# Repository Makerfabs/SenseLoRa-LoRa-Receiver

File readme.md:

# SENSELORA LORA RECEIVER

```c++
/*
Version:		V1.0
Author:			Vincent
Create Date:	2023/9/16
Note:

*/
```
# Makerfabs

[Makerfabs home page](https://www.makerfabs.com/)

[Makerfabs Wiki](https://wiki.makerfabs.com/)

# How To Use

## Arduino Complier Option

**If you have any questions，such as how to install the development board, how to download the code, how to install the library. Please refer to :[Makerfabs_FAQ](https://github.com/Makerfabs/Makerfabs_FAQ)**

- Please disconnect from the electrical equipment before burning!
- Do not burn with alternating current!
- Open Arduino IDE
- Open boards Manager, search "RP2040"
- Install board:  Arduino Mbed OS RP2040 Boards(Version 4.0.4)

Arduino libraries:

- RP2040_SD 1.0.1  
- RadioLib 4.6.0  
- Adafruit_GFX_Library 1.11.5  
- Adafruit_BusIO 1.14.1  
- Adafruit_SSD1306 2.5.1  

## Data Analysis

Once the device is plugged in, run data_analysis.py and the serial port will be found automatically. In addition, the json data uploaded by the device is classified according to ID and stored into different CSV files.

Make sure that no other serial device is connected, or modify the Python program yourself.

Environment:

- Python      3.11.2
- pyserial    3.5

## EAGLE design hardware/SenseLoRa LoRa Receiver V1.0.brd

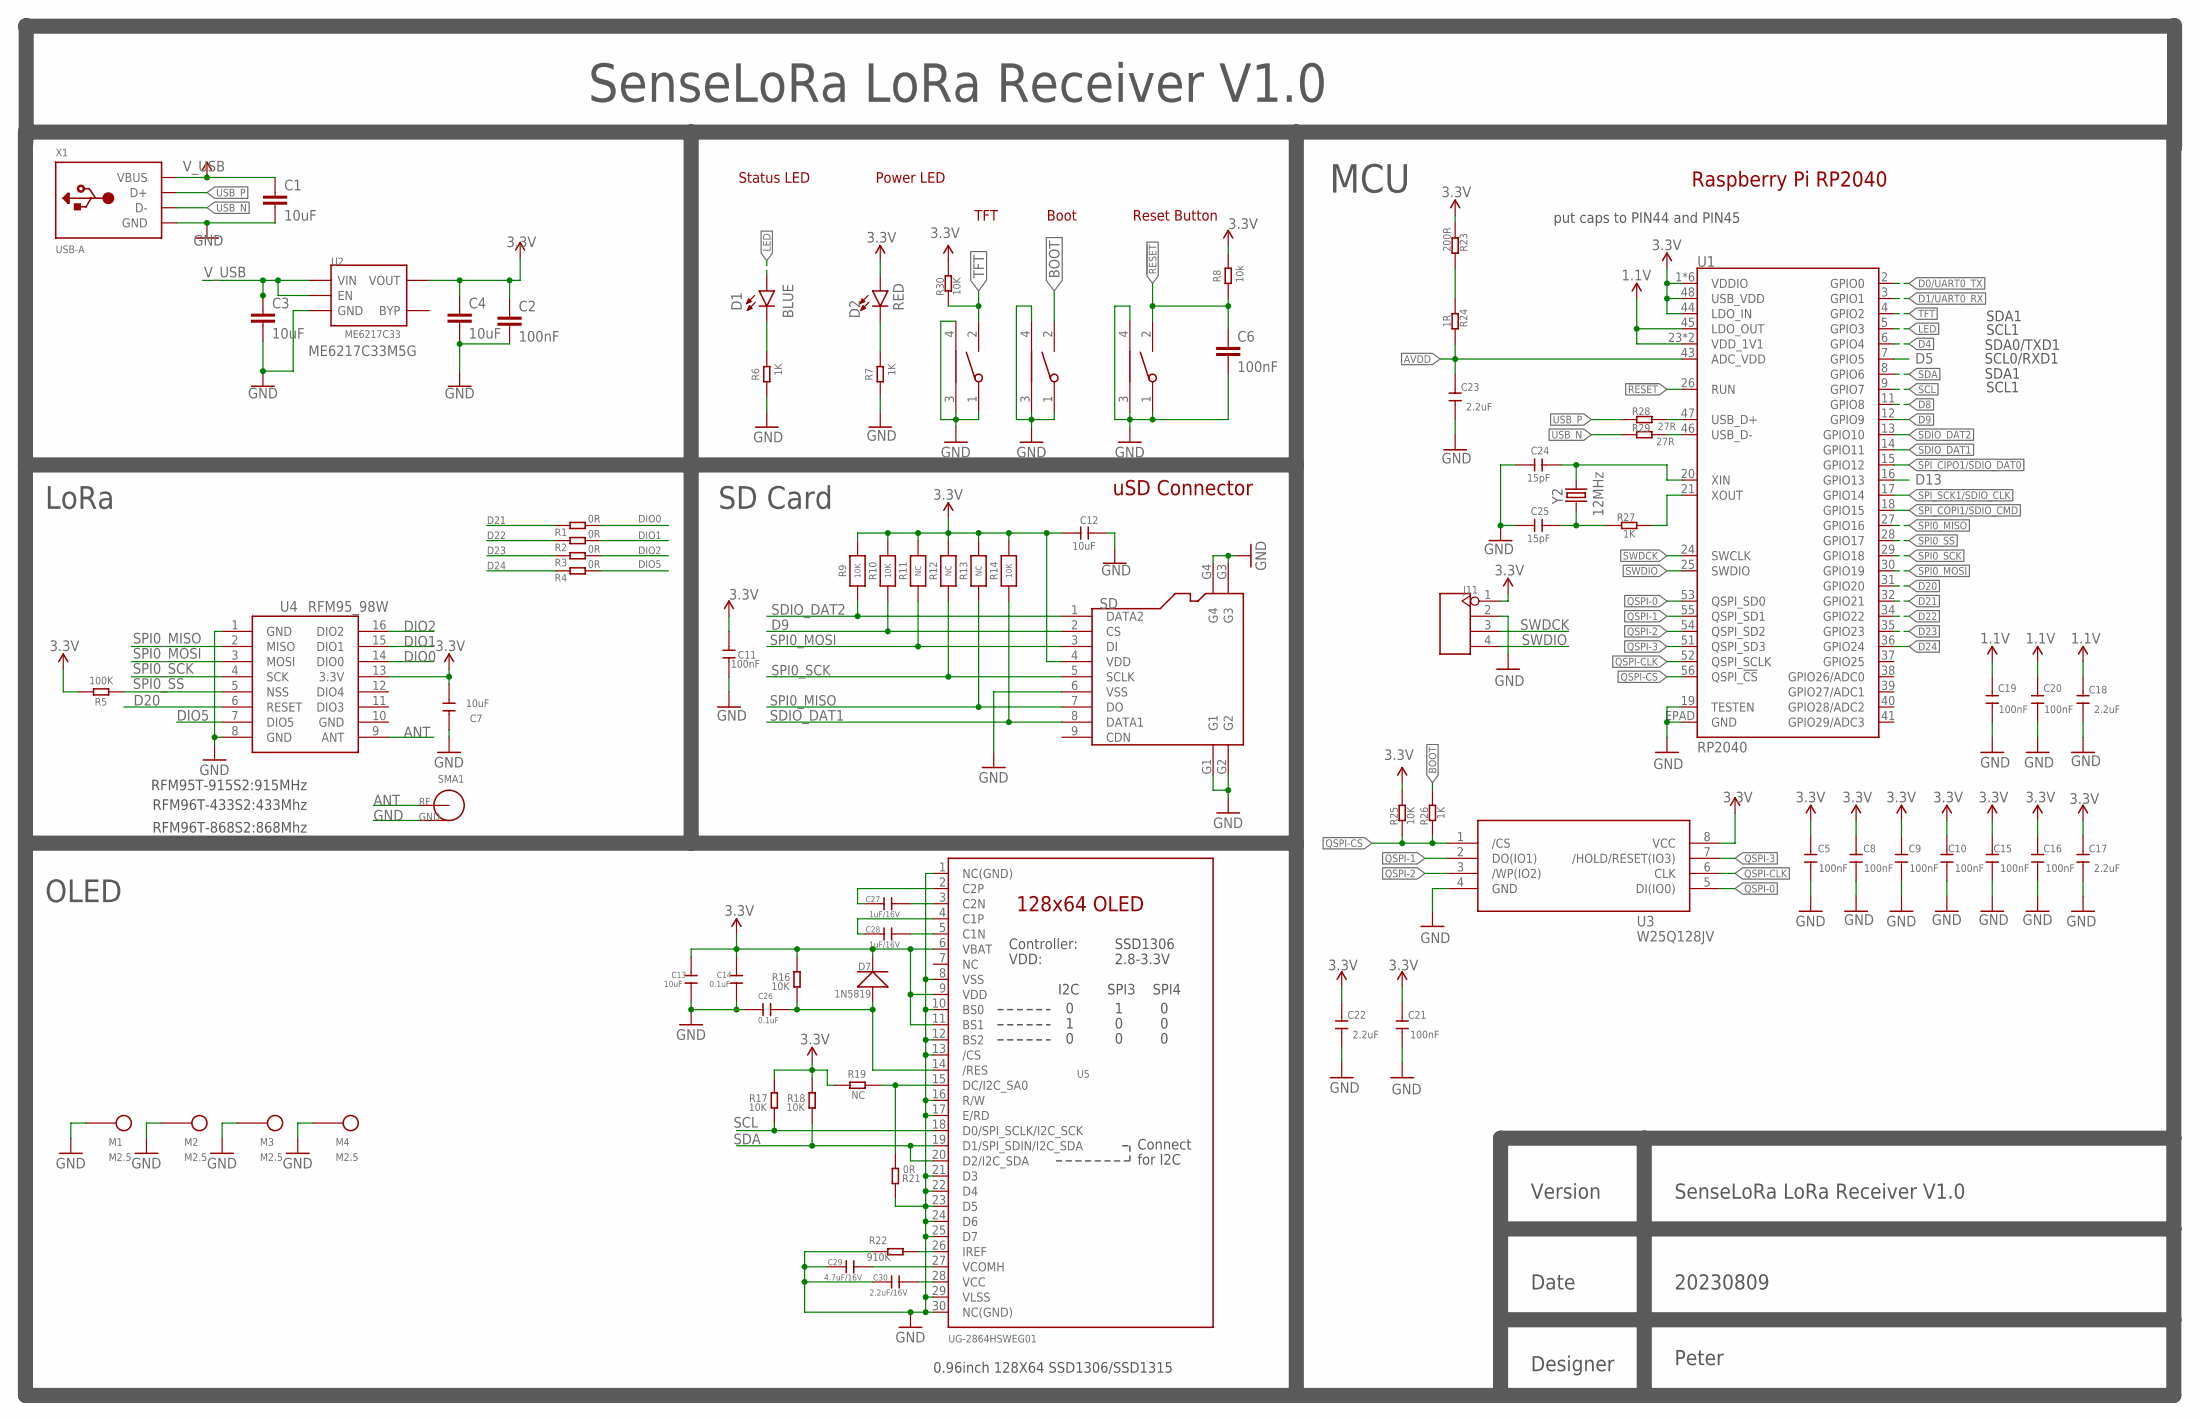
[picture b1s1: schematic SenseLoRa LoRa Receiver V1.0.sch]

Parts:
BOOT: TS24CA; 2*4*3.5MM
C1, C3, C4, C7, C13: 10uF; C0603
C2, C5, C6, C8, C9, C10, C11, C15, C16, C19, C20, C21: 100nF; C0603
C12: 10uF; DISCRETE_C0603
C14, C26: 0.1uF; C0603
C17, C18, C22, C23: 2.2uF; C0603
C24, C25: 15pF; C0603
C27, C28: 1uF/16V; C0603
C29: 4.7uF/16V; C0603
C30: 2.2uF/16V; C0603
D1: BLUE; LED-0603
D2: RED; LED-0603
D7: 1N5819; SOD323
J11: HEADER-4P-60/35MILROUND; 4P-65/35ROUND
M1, M2, M3, M4: M2.5
R1, R2, R3, R4, R21: 0R; 0603
R5: 100K; 0603
R6, R7, R26, R27: 1K; 0603
R8: 10k; 0603
R9, R10, R14: 10K; 0603-NO
R11, R12, R13: NC; 0603-NO
R16, R17, R18, R25, R30: 10K; 0603
R19: NC; 0603
R22: 910K; 0603
R23: 200R; 0603
R24: 1R; 0603
R28, R29: 27R; 0603
RST: TS24CA; 2*4*3.5MM
SD: HOLDER-MICROSD-9P; 9P-SMD-W/-RING
SMA1: SMA-KWE
TFT: TS24CA; 2*4*3.5MM
U1: RP2040; QFN-56
U2: ME6217C33; SOT23-5
U3: W25Q128JV; SOIC-8-208MIL
U4: RFM95_98W; RFM92_93W
U5: UG-2864HSWEG01; UG-2864HSWEG01_0.96IN_WRAPAROUND
X1: USB-A; MOLEX_480371000
Y2: 12MHz; CRYSTAL-SMD-2X2.5MM

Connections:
1.1V: C18.2, C19.2, C20.2, U1.23 (VDD_1V1), U1.45 (LDO_OUT), U1.50 (VDD_1V1)
3.3V: C2.1, C4.1, C5.2, C7.2, C8.2, C9.2, C10.2, C11.2, C12.2, C13.1, C14.1, C15.2, C16.2, C17.2, C21.2, C22.2, D2.A, D7.-, J11.1, R5.2, R8.1, R9.2, R10.2, R11.2, R12.2, R13.2, R14.2, R16.2, R17.2, R18.2, R19.2, R23.2, R25.1, R30.1, SD.4 (VDD), U1.1 (VDDIO), U1.10 (VDDIO), U1.22 (VDDIO), U1.33 (VDDIO), U1.42 (VDDIO), U1.44 (LDO_IN), U1.48 (USB_VDD), U1.49 (VDDIO), U2.5 (VOUT), U3.8 (VCC), U4.13 (3.3V), U5.6 (VBAT), U5.9 (VDD), U5.11 (BS1)
!RESET!: C6.1, R8.2, RST.2, U1.26 (RUN)
ADC_VREF: R23.1, R24.2
ANT: SMA1.1 (SIG), U4.9 (ANT)
AVDD: C23.2, R24.1, U1.43 (ADC_VDD)
BOOT: BOOT.2, R26.1
D0/UART0_TX: U1.2 (GPIO0)
D1/UART0_RX: U1.3 (GPIO1)
D4: U1.6 (GPIO4)
D5: U1.7 (GPIO5)
D8: U1.11 (GPIO8)
D9: R10.1, SD.2 (CS), U1.12 (GPIO9)
D13: U1.16 (GPIO13)
D20: U1.31 (GPIO20), U4.6 (RESET)
D21: R1.2, U1.32 (GPIO21)
D22: R2.2, U1.34 (GPIO22)
D23: R3.2, U1.35 (GPIO23)
D24: R4.2, U1.36 (GPIO24)
DIO0: R1.1, U4.14 (DIO0)
DIO1: R2.1, U4.15 (DIO1)
DIO2: R3.1, U4.16 (DIO2)
DIO5: R4.1, U4.7 (DIO5)
GND: BOOT.1, BOOT.3, BOOT.4, C1.2, C2.2, C3.2, C4.2, C5.1, C6.2, C7.1, C8.1, C9.1, C10.1, C11.1, C12.1, C13.2, C14.2, C15.1, C16.1, C17.1, C18.1, C19.1, C20.1, C21.1, C22.1, C23.1, C24.2, C25.2, C26.1, C29.1, C30.1, J11.2, M1.1, M2.1, M3.1, M4.1, R6.2, R7.2, R21.2, R22.2, RST.1, RST.3, RST.4, SD.6 (VSS), SD.G1, SD.G2, SD.G3, SD.G4, SMA1.2 (GND), SMA1.3 (GND), SMA1.4 (GND), SMA1.5 (GND), TFT.1, TFT.3, TFT.4, U1.19 (TESTEN), U1.EPAD (GND), U2.2 (GND), U3.4 (GND), U4.1 (GND), U4.8 (GND), U4.10 (GND), U5.1 (NC(GND)), U5.8 (VSS), U5.10 (BS0), U5.12 (BS2), U5.13 (/CS), U5.16 (R/W), U5.17 (E/RD), U5.21 (D3), U5.22 (D4), U5.23 (D5), U5.24 (D6), U5.25 (D7), U5.29 (VLSS), U5.30 (NC(GND)), X1.4 (GND)
LED: D1.A, U1.5 (GPIO3)
unnamed: C24.1, U1.20 (XIN), Y2.P3 (2)
unnamed: D1.C, R6.1
unnamed: R19.1, R21.1, U5.15 (DC/I2C_SA0)
unnamed: R27.1, U1.21 (XOUT)
unnamed: C29.2, U5.27 (VCOMH)
unnamed: C25.1, R27.2, Y2.P1 (1)
unnamed: D2.C, R7.1
unnamed: C30.2, U5.28 (VCC)
unnamed: R22.1, U5.26 (IREF)
unnamed: C27.2, U5.3 (C2N)
unnamed: C27.1, U5.2 (C2P)
unnamed: C28.1, U5.4 (C1P)
unnamed: C28.2, U5.5 (C1N)
unnamed: C26.2, D7.+, R16.1, U5.14 (/RES)
QSPI-0: U1.53 (QSPI_SD0), U3.5 (DI(IO0))
QSPI-1: U1.55 (QSPI_SD1), U3.2 (DO(IO1))
QSPI-2: U1.54 (QSPI_SD2), U3.3 (/WP(IO2))
QSPI-3: U1.51 (QSPI_SD3), U3.7 (/HOLD/RESET(IO3))
QSPI-CLK: U1.52 (QSPI_SCLK), U3.6 (CLK)
QSPI-CS: R25.2, R26.2, U1.56 (QSPI_!CS!), U3.1 (/CS)
SCL: R17.1, U1.9 (GPIO7), U5.18 (D0/SPI_SCLK/I2C_SCK)
SDA: R18.1, U1.8 (GPIO6), U5.19 (D1/SPI_SDIN/I2C_SDA), U5.20 (D2/I2C_SDA)
SDIO_DAT1: R14.1, SD.8 (DATA1), U1.14 (GPIO11)
SDIO_DAT2: R9.1, SD.1 (DATA2), U1.13 (GPIO10)
SPI0_MISO: R13.1, SD.7 (DO), U1.27 (GPIO16), U4.2 (MISO)
SPI0_MOSI: R11.1, SD.3 (DI), U1.30 (GPIO19), U4.3 (MOSI)
SPI0_SCK: R12.1, SD.5 (SCLK), U1.29 (GPIO18), U4.4 (SCK)
SPI0_SS: R5.1, U1.28 (GPIO17), U4.5 (NSS)
SPI_CIPO1/SDIO_DAT0: U1.15 (GPIO12)
SPI_COPI1/SDIO_CMD: U1.18 (GPIO15)
SPI_SCK1/SDIO_CLK: U1.17 (GPIO14)
SWDCK: J11.3, U1.24 (SWCLK)
SWDIO: J11.4, U1.25 (SWDIO)
TFT: R30.2, TFT.2, U1.4 (GPIO2)
USB_F_N: R29.1, U1.46 (USB_D-)
USB_F_P: R28.1, U1.47 (USB_D+)
USB_N: R29.2, X1.2 (D-)
USB_P: R28.2, X1.3 (D+)
V_USB: C1.1, C3.1, U2.1 (VIN), U2.3 (EN), X1.1 (VBUS)

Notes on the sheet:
RFM95T-915S2:915MHz
RFM96T-433S2:433Mhz
uSD Connector
Raspberry Pi RP2040
Reset Button
Status LED
Boot
Power LED
put caps to PIN44 and PIN45
SDA0/TXD1
SCL0/RXD1
SDA1
SCL1
RFM96T-868S2:868Mhz
LoRa
MCU
SenseLoRa LoRa Receiver V1.0
Version
Date
Designer
20230809
Peter
ME6217C33M5G
SD Card
0.96inch 128X64 SSD1306/SSD1315
OLED
TFT

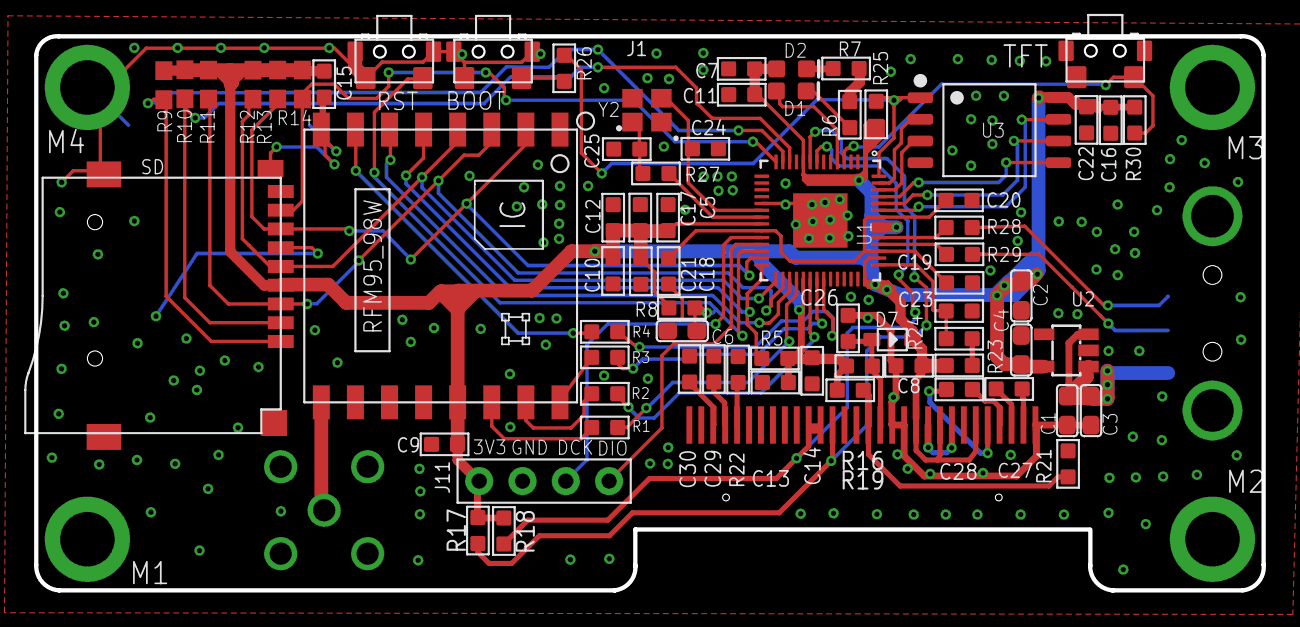
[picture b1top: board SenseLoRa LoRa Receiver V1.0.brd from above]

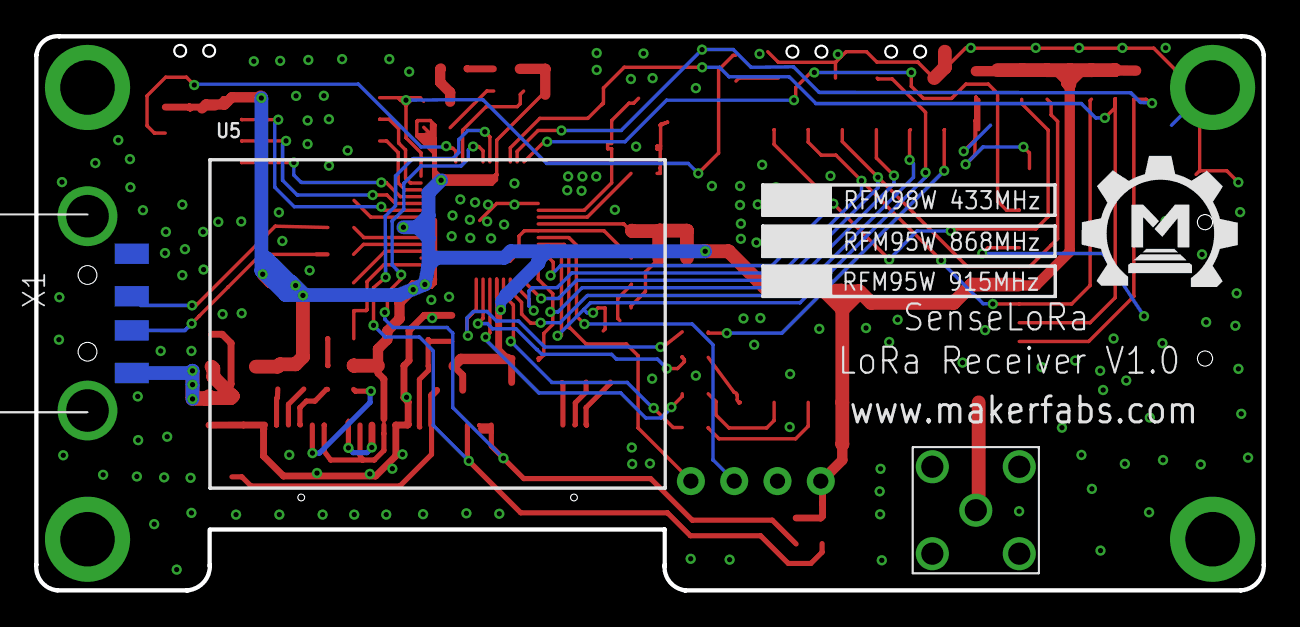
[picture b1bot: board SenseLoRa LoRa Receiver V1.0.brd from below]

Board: 2 copper layers, 72.0 x 32.5 mm, 79 parts (4 on the bottom side), 55 nets.

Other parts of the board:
U$1: MAKERFABS_0.3

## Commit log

2023-09-16 Create
2023-09-16 Change file name
2023-09-16 Edit Readme
2023-09-18 Add hardware
2023-09-25 Add mac support

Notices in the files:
parts and their libraries:
microbuilder: This work is placed in the public domain, and may be freely used for commercial and non-commercial work with the following conditions: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
SparkFun-Clocks: Licensing: Creative Commons ShareAlike 4.0 International - https://creativecommons.org/licenses/by-sa/4.0
